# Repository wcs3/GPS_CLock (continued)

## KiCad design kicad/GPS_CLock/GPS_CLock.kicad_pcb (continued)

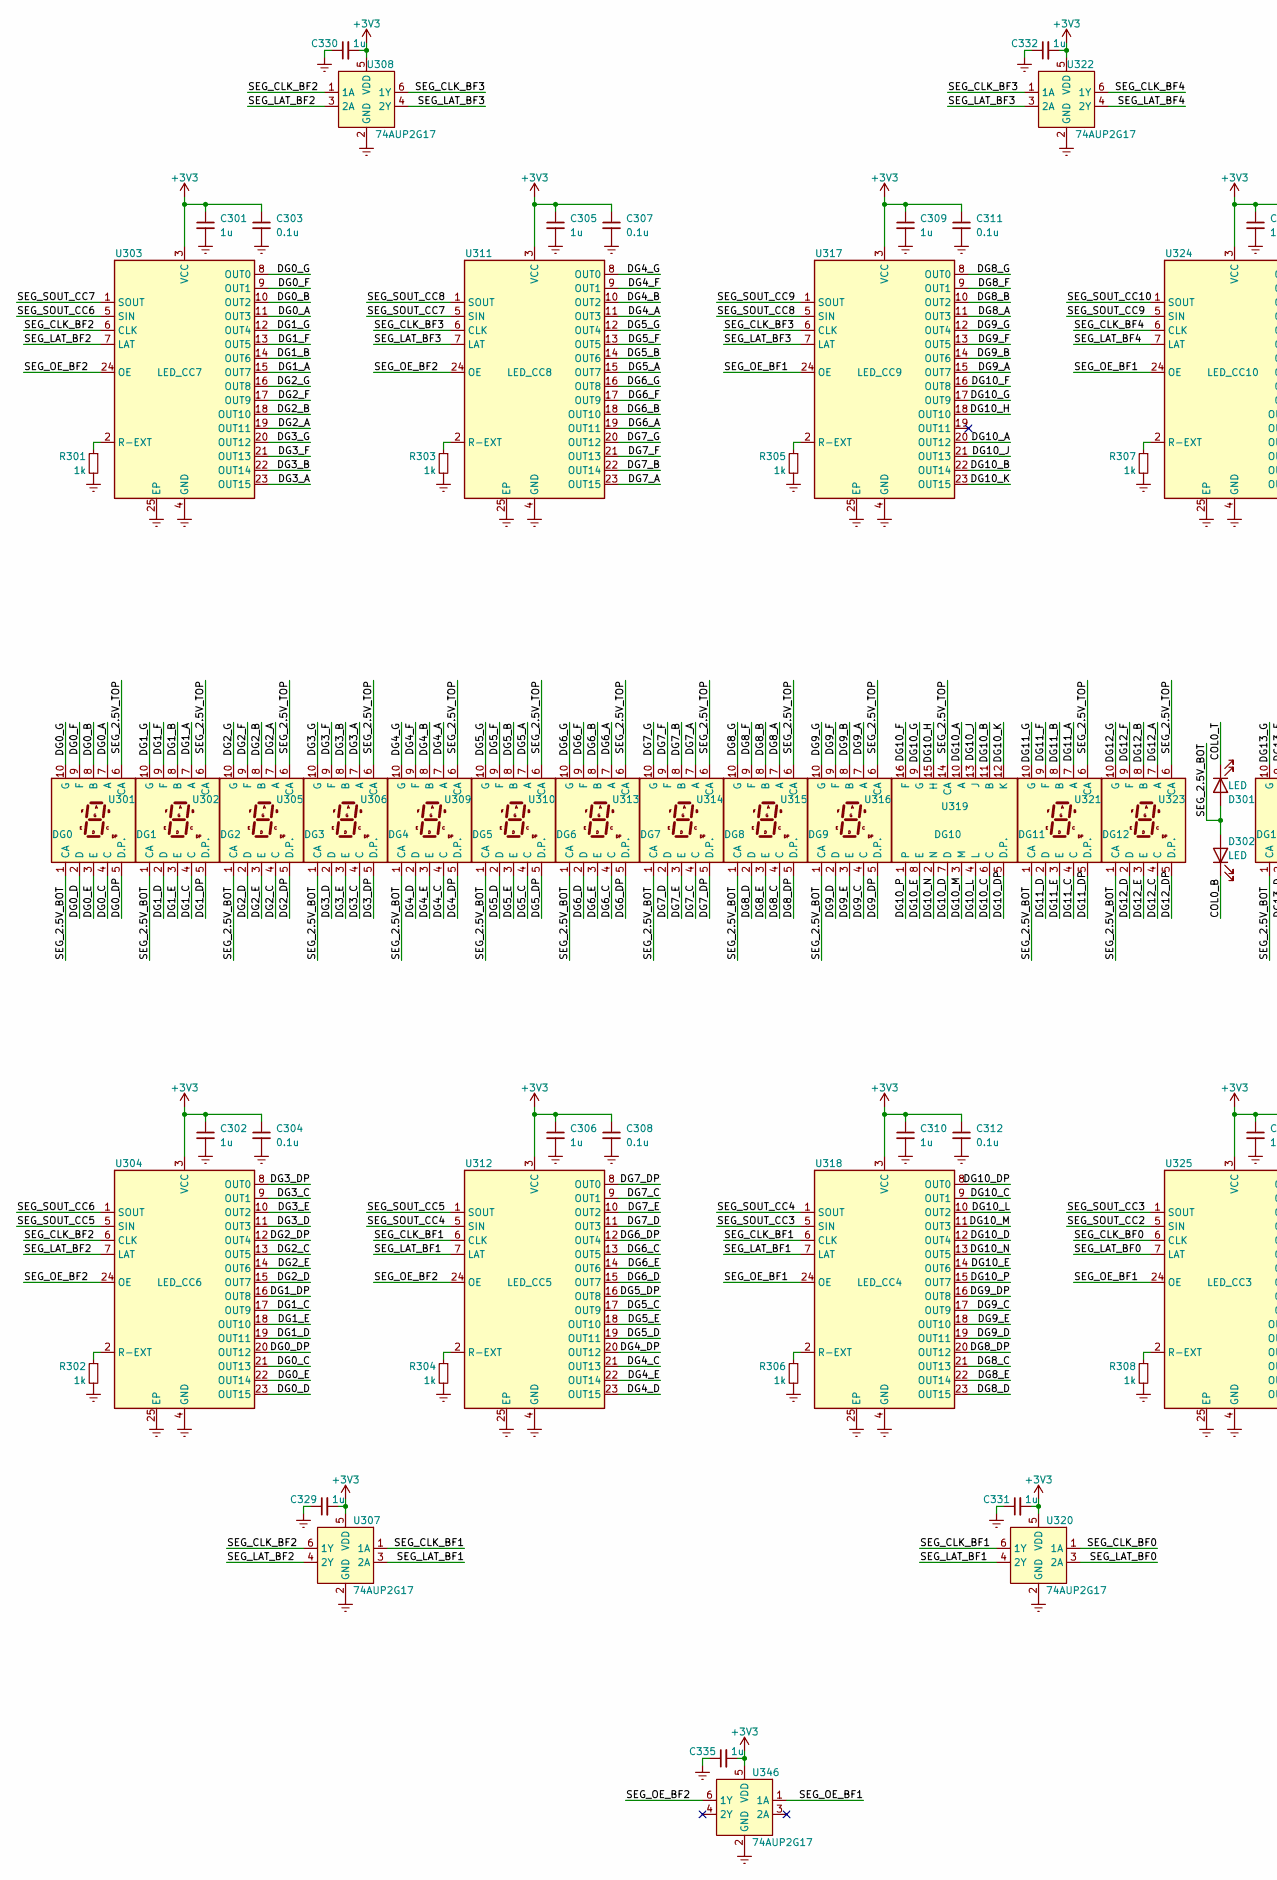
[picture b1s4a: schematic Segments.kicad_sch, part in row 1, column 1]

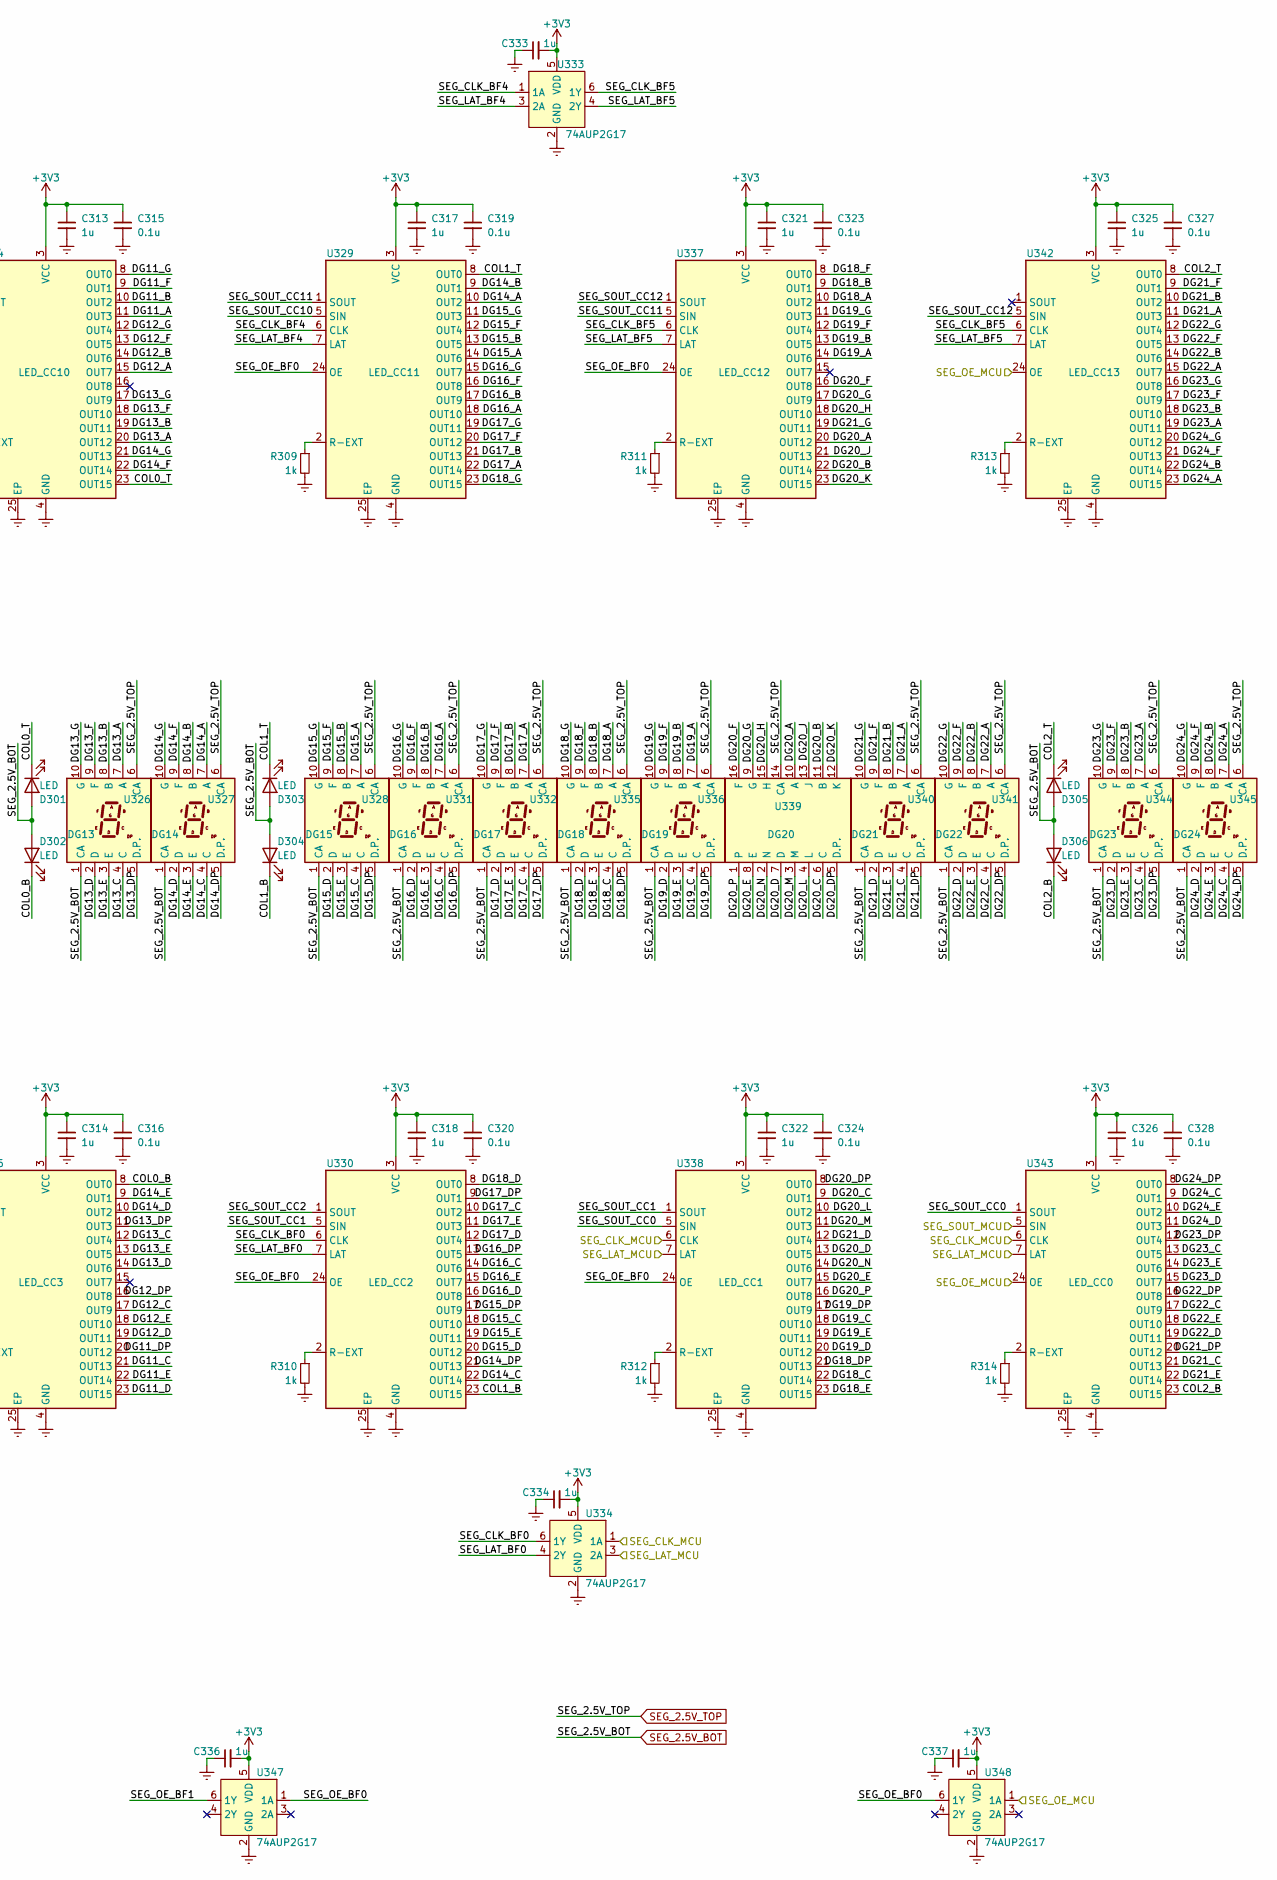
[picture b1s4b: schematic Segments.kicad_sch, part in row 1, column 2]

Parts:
C301, C302, C305, C306, C309, C310, C313, C314, C317, C318, C321, C322, C325, C326, C329, C330, C331, C332, C333, C334, C335, C336, C337: 1u; C_0402_1005Metric
C303, C304, C307, C308, C311, C312, C315, C316, C319, C320, C323, C324, C327, C328: 0.1u; C_0402_1005Metric
D301, D302, D303, D304, D305, D306: LED; LED_0805_2012Metric
R301, R302, R303, R304, R305, R306, R307, R308, R309, R310, R311, R312, R313, R314: 1k; R_0402_1005Metric
U301: DG0; 7seg 0.8in smd
U302: DG1; 7seg 0.8in smd
U303: LED_CC7; QFN-24-1EP_4x4mm_P0.5mm_EP2.6x2.6mm
U304: LED_CC6; QFN-24-1EP_4x4mm_P0.5mm_EP2.6x2.6mm
U305: DG2; 7seg 0.8in smd
U306: DG3; 7seg 0.8in smd
U307, U308, U320, U322, U333, U334, U346, U347, U348: 74AUP2G17; XSON-6_SOT886
U309: DG4; 7seg 0.8in smd
U310: DG5; 7seg 0.8in smd
U311: LED_CC8; QFN-24-1EP_4x4mm_P0.5mm_EP2.6x2.6mm
U312: LED_CC5; QFN-24-1EP_4x4mm_P0.5mm_EP2.6x2.6mm
U313: DG6; 7seg 0.8in smd
U314: DG7; 7seg 0.8in smd
U315: DG8; 7seg 0.8in smd
U316: DG9; 7seg 0.8in smd
U317: LED_CC9; QFN-24-1EP_4x4mm_P0.5mm_EP2.6x2.6mm
U318: LED_CC4; QFN-24-1EP_4x4mm_P0.5mm_EP2.6x2.6mm
U319: DG10; 14seg 0.4in smd
U321: DG11; 7seg 0.8in smd
U323: DG12; 7seg 0.8in smd
U324: LED_CC10; QFN-24-1EP_4x4mm_P0.5mm_EP2.6x2.6mm
U325: LED_CC3; QFN-24-1EP_4x4mm_P0.5mm_EP2.6x2.6mm
U326: DG13; 7seg 0.8in smd
U327: DG14; 7seg 0.8in smd
U328: DG15; 7seg 0.8in smd
U329: LED_CC11; QFN-24-1EP_4x4mm_P0.5mm_EP2.6x2.6mm
U330: LED_CC2; QFN-24-1EP_4x4mm_P0.5mm_EP2.6x2.6mm
U331: DG16; 7seg 0.8in smd
U332: DG17; 7seg 0.8in smd
U335: DG18; 7seg 0.8in smd
U336: DG19; 7seg 0.8in smd
U337: LED_CC12; QFN-24-1EP_4x4mm_P0.5mm_EP2.6x2.6mm
U338: LED_CC1; QFN-24-1EP_4x4mm_P0.5mm_EP2.6x2.6mm
U339: DG20; 14seg 0.4in smd
U340: DG21; 7seg 0.8in smd
U341: DG22; 7seg 0.8in smd
U342: LED_CC13; QFN-24-1EP_4x4mm_P0.5mm_EP2.6x2.6mm
U343: LED_CC0; QFN-24-1EP_4x4mm_P0.5mm_EP2.6x2.6mm
U344: DG23; 7seg 0.8in smd
U345: DG24; 7seg 0.8in smd

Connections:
+3V3: C301.1, C302.1, C303.1, C304.1, C305.1, C306.1, C307.1, C308.1, C309.1, C310.1, C311.1, C312.1, C313.1, C314.1, C315.1, C316.1, C317.1, C318.1, C319.1, C320.1, C321.1, C322.1, C323.1, C324.1, C325.1, C326.1, C327.1, C328.1, C329.2, C330.2, C331.2, C332.2, C333.2, C334.2, C335.2, C336.2, C337.2, U303.3 (VCC), U304.3 (VCC), U307.5 (VDD), U308.5 (VDD), U311.3 (VCC), U312.3 (VCC), U317.3 (VCC), U318.3 (VCC), U320.5 (VDD), U322.5 (VDD), U324.3 (VCC), U325.3 (VCC), U329.3 (VCC), U330.3 (VCC), U333.5 (VDD), U334.5 (VDD), U337.3 (VCC), U338.3 (VCC), U342.3 (VCC), U343.3 (VCC), U346.5 (VDD), U347.5 (VDD), U348.5 (VDD); also elsewhere on the board
/SEG_CLK: U334.1 (1A), U338.6 (CLK), U343.6 (CLK); also elsewhere on the board
/SEG_LAT: U334.3 (2A), U338.7 (LAT), U343.7 (LAT); also elsewhere on the board
/SEG_MOSI: U343.5 (SIN); also elsewhere on the board
/SEG_OE: U342.24 (OE), U343.24 (OE), U348.1 (1A); also elsewhere on the board
/Segments/COL0_B: D302.1 (K), U325.8 (OUT0)
/Segments/COL0_T: D301.1 (K), U324.23 (OUT15)
/Segments/COL1_B: D304.1 (K), U330.23 (OUT15)
/Segments/COL1_T: D303.1 (K), U329.8 (OUT0)
/Segments/COL2_B: D306.1 (K), U343.23 (OUT15)
/Segments/COL2_T: D305.1 (K), U342.8 (OUT0)
/Segments/DG0_A: U301.7 (A), U303.11 (OUT3)
/Segments/DG0_B: U301.8 (B), U303.10 (OUT2)
/Segments/DG0_C: U301.4 (C), U304.21 (OUT13)
/Segments/DG0_D: U301.2 (D), U304.23 (OUT15)
/Segments/DG0_DP: U301.5 (D.P.), U304.20 (OUT12)
/Segments/DG0_E: U301.3 (E), U304.22 (OUT14)
/Segments/DG0_F: U301.9 (F), U303.9 (OUT1)
/Segments/DG0_G: U301.10 (G), U303.8 (OUT0)
/Segments/DG1_A: U302.7 (A), U303.15 (OUT7)
/Segments/DG1_B: U302.8 (B), U303.14 (OUT6)
/Segments/DG1_C: U302.4 (C), U304.17 (OUT9)
/Segments/DG1_D: U302.2 (D), U304.19 (OUT11)
/Segments/DG1_DP: U302.5 (D.P.), U304.16 (OUT8)
/Segments/DG1_E: U302.3 (E), U304.18 (OUT10)
/Segments/DG1_F: U302.9 (F), U303.13 (OUT5)
/Segments/DG1_G: U302.10 (G), U303.12 (OUT4)
/Segments/DG2_A: U303.19 (OUT11), U305.7 (A)
/Segments/DG2_B: U303.18 (OUT10), U305.8 (B)
/Segments/DG2_C: U304.13 (OUT5), U305.4 (C)
/Segments/DG2_D: U304.15 (OUT7), U305.2 (D)
/Segments/DG2_DP: U304.12 (OUT4), U305.5 (D.P.)
/Segments/DG2_E: U304.14 (OUT6), U305.3 (E)
/Segments/DG2_F: U303.17 (OUT9), U305.9 (F)
/Segments/DG2_G: U303.16 (OUT8), U305.10 (G)
/Segments/DG3_A: U303.23 (OUT15), U306.7 (A)
/Segments/DG3_B: U303.22 (OUT14), U306.8 (B)
/Segments/DG3_C: U304.9 (OUT1), U306.4 (C)
/Segments/DG3_D: U304.11 (OUT3), U306.2 (D)
/Segments/DG3_DP: U304.8 (OUT0), U306.5 (D.P.)
/Segments/DG3_E: U304.10 (OUT2), U306.3 (E)
/Segments/DG3_F: U303.21 (OUT13), U306.9 (F)
/Segments/DG3_G: U303.20 (OUT12), U306.10 (G)
/Segments/DG4_A: U309.7 (A), U311.11 (OUT3)
/Segments/DG4_B: U309.8 (B), U311.10 (OUT2)
/Segments/DG4_C: U309.4 (C), U312.21 (OUT13)
/Segments/DG4_D: U309.2 (D), U312.23 (OUT15)
/Segments/DG4_DP: U309.5 (D.P.), U312.20 (OUT12)
/Segments/DG4_E: U309.3 (E), U312.22 (OUT14)
/Segments/DG4_F: U309.9 (F), U311.9 (OUT1)
/Segments/DG4_G: U309.10 (G), U311.8 (OUT0)
/Segments/DG5_A: U310.7 (A), U311.15 (OUT7)
/Segments/DG5_B: U310.8 (B), U311.14 (OUT6)
/Segments/DG5_C: U310.4 (C), U312.17 (OUT9)
/Segments/DG5_D: U310.2 (D), U312.19 (OUT11)
/Segments/DG5_DP: U310.5 (D.P.), U312.16 (OUT8)
/Segments/DG5_E: U310.3 (E), U312.18 (OUT10)
/Segments/DG5_F: U310.9 (F), U311.13 (OUT5)
/Segments/DG5_G: U310.10 (G), U311.12 (OUT4)
/Segments/DG6_A: U311.19 (OUT11), U313.7 (A)
/Segments/DG6_B: U311.18 (OUT10), U313.8 (B)
/Segments/DG6_C: U312.13 (OUT5), U313.4 (C)
/Segments/DG6_D: U312.15 (OUT7), U313.2 (D)
/Segments/DG6_DP: U312.12 (OUT4), U313.5 (D.P.)
/Segments/DG6_E: U312.14 (OUT6), U313.3 (E)
/Segments/DG6_F: U311.17 (OUT9), U313.9 (F)
/Segments/DG6_G: U311.16 (OUT8), U313.10 (G)
/Segments/DG7_A: U311.23 (OUT15), U314.7 (A)
/Segments/DG7_B: U311.22 (OUT14), U314.8 (B)
/Segments/DG7_C: U312.9 (OUT1), U314.4 (C)
/Segments/DG7_D: U312.11 (OUT3), U314.2 (D)
/Segments/DG7_DP: U312.8 (OUT0), U314.5 (D.P.)
/Segments/DG7_E: U312.10 (OUT2), U314.3 (E)
/Segments/DG7_F: U311.21 (OUT13), U314.9 (F)
/Segments/DG7_G: U311.20 (OUT12), U314.10 (G)
/Segments/DG8_A: U315.7 (A), U317.11 (OUT3)
/Segments/DG8_B: U315.8 (B), U317.10 (OUT2)
/Segments/DG8_C: U315.4 (C), U318.21 (OUT13)
/Segments/DG8_D: U315.2 (D), U318.23 (OUT15)
/Segments/DG8_DP: U315.5 (D.P.), U318.20 (OUT12)
/Segments/DG8_E: U315.3 (E), U318.22 (OUT14)
/Segments/DG8_F: U315.9 (F), U317.9 (OUT1)
/Segments/DG8_G: U315.10 (G), U317.8 (OUT0)
/Segments/DG9_A: U316.7 (A), U317.15 (OUT7)
/Segments/DG9_B: U316.8 (B), U317.14 (OUT6)
/Segments/DG9_C: U316.4 (C), U318.17 (OUT9)
/Segments/DG9_D: U316.2 (D), U318.19 (OUT11)
/Segments/DG9_DP: U316.5 (D.P.), U318.16 (OUT8)
/Segments/DG9_E: U316.3 (E), U318.18 (OUT10)
/Segments/DG9_F: U316.9 (F), U317.13 (OUT5)
/Segments/DG9_G: U316.10 (G), U317.12 (OUT4)
/Segments/DG10_A: U317.20 (OUT12), U319.10 (A)
/Segments/DG10_B: U317.22 (OUT14), U319.11 (B)
/Segments/DG10_C: U318.9 (OUT1), U319.6 (C)
/Segments/DG10_D: U318.12 (OUT4), U319.7 (D)
/Segments/DG10_DP: U318.8 (OUT0), U319.5 (D.P.)
/Segments/DG10_E: U318.14 (OUT6), U319.8 (E)
/Segments/DG10_F: U317.16 (OUT8), U319.16 (F)
/Segments/DG10_G: U317.17 (OUT9), U319.9 (G)
/Segments/DG10_H: U317.18 (OUT10), U319.15 (H)
/Segments/DG10_J: U317.21 (OUT13), U319.13 (J)
/Segments/DG10_K: U317.23 (OUT15), U319.12 (K)
/Segments/DG10_L: U318.10 (OUT2), U319.4 (L)
/Segments/DG10_M: U318.11 (OUT3), U319.3 (M)
/Segments/DG10_N: U318.13 (OUT5), U319.2 (N)
/Segments/DG10_P: U318.15 (OUT7), U319.1
/Segments/DG11_A: U321.7 (A), U324.11 (OUT3)
/Segments/DG11_B: U321.8 (B), U324.10 (OUT2)
/Segments/DG11_C: U321.4 (C), U325.21 (OUT13)
/Segments/DG11_D: U321.2 (D), U325.23 (OUT15)
/Segments/DG11_DP: U321.5 (D.P.), U325.20 (OUT12)
/Segments/DG11_E: U321.3 (E), U325.22 (OUT14)
/Segments/DG11_F: U321.9 (F), U324.9 (OUT1)
/Segments/DG11_G: U321.10 (G), U324.8 (OUT0)
/Segments/DG12_A: U323.7 (A), U324.15 (OUT7)
/Segments/DG12_B: U323.8 (B), U324.14 (OUT6)
/Segments/DG12_C: U323.4 (C), U325.17 (OUT9)
/Segments/DG12_D: U323.2 (D), U325.19 (OUT11)
/Segments/DG12_DP: U323.5 (D.P.), U325.16 (OUT8)
/Segments/DG12_E: U323.3 (E), U325.18 (OUT10)
/Segments/DG12_F: U323.9 (F), U324.13 (OUT5)
/Segments/DG12_G: U323.10 (G), U324.12 (OUT4)
/Segments/DG13_A: U324.20 (OUT12), U326.7 (A)
/Segments/DG13_B: U324.19 (OUT11), U326.8 (B)
/Segments/DG13_C: U325.12 (OUT4), U326.4 (C)
/Segments/DG13_D: U325.14 (OUT6), U326.2 (D)
/Segments/DG13_DP: U325.11 (OUT3), U326.5 (D.P.)
/Segments/DG13_E: U325.13 (OUT5), U326.3 (E)
/Segments/DG13_F: U324.18 (OUT10), U326.9 (F)
/Segments/DG13_G: U324.17 (OUT9), U326.10 (G)
/Segments/DG14_A: U327.7 (A), U329.10 (OUT2)
/Segments/DG14_B: U327.8 (B), U329.9 (OUT1)
/Segments/DG14_C: U327.4 (C), U330.22 (OUT14)
/Segments/DG14_D: U325.10 (OUT2), U327.2 (D)
/Segments/DG14_DP: U327.5 (D.P.), U330.21 (OUT13)
/Segments/DG14_E: U325.9 (OUT1), U327.3 (E)
/Segments/DG14_F: U324.22 (OUT14), U327.9 (F)
/Segments/DG14_G: U324.21 (OUT13), U327.10 (G)
/Segments/DG15_A: U328.7 (A), U329.14 (OUT6)
/Segments/DG15_B: U328.8 (B), U329.13 (OUT5)
/Segments/DG15_C: U328.4 (C), U330.18 (OUT10)
/Segments/DG15_D: U328.2 (D), U330.20 (OUT12)
/Segments/DG15_DP: U328.5 (D.P.), U330.17 (OUT9)
/Segments/DG15_E: U328.3 (E), U330.19 (OUT11)
/Segments/DG15_F: U328.9 (F), U329.12 (OUT4)
/Segments/DG15_G: U328.10 (G), U329.11 (OUT3)
/Segments/DG16_A: U329.18 (OUT10), U331.7 (A)
/Segments/DG16_B: U329.17 (OUT9), U331.8 (B)
/Segments/DG16_C: U330.14 (OUT6), U331.4 (C)
/Segments/DG16_D: U330.16 (OUT8), U331.2 (D)
/Segments/DG16_DP: U330.13 (OUT5), U331.5 (D.P.)
/Segments/DG16_E: U330.15 (OUT7), U331.3 (E)
/Segments/DG16_F: U329.16 (OUT8), U331.9 (F)
/Segments/DG16_G: U329.15 (OUT7), U331.10 (G)
/Segments/DG17_A: U329.22 (OUT14), U332.7 (A)
/Segments/DG17_B: U329.21 (OUT13), U332.8 (B)
/Segments/DG17_C: U330.10 (OUT2), U332.4 (C)
/Segments/DG17_D: U330.12 (OUT4), U332.2 (D)
/Segments/DG17_DP: U330.9 (OUT1), U332.5 (D.P.)
/Segments/DG17_E: U330.11 (OUT3), U332.3 (E)
/Segments/DG17_F: U329.20 (OUT12), U332.9 (F)
/Segments/DG17_G: U329.19 (OUT11), U332.10 (G)
/Segments/DG18_A: U335.7 (A), U337.10 (OUT2)
/Segments/DG18_B: U335.8 (B), U337.9 (OUT1)
/Segments/DG18_C: U335.4 (C), U338.22 (OUT14)
/Segments/DG18_D: U330.8 (OUT0), U335.2 (D)
/Segments/DG18_DP: U335.5 (D.P.), U338.21 (OUT13)
/Segments/DG18_E: U335.3 (E), U338.23 (OUT15)
/Segments/DG18_F: U335.9 (F), U337.8 (OUT0)
/Segments/DG18_G: U329.23 (OUT15), U335.10 (G)
/Segments/DG19_A: U336.7 (A), U337.14 (OUT6)
/Segments/DG19_B: U336.8 (B), U337.13 (OUT5)
/Segments/DG19_C: U336.4 (C), U338.18 (OUT10)
/Segments/DG19_D: U336.2 (D), U338.20 (OUT12)
/Segments/DG19_DP: U336.5 (D.P.), U338.17 (OUT9)
/Segments/DG19_E: U336.3 (E), U338.19 (OUT11)
/Segments/DG19_F: U336.9 (F), U337.12 (OUT4)
/Segments/DG19_G: U336.10 (G), U337.11 (OUT3)
/Segments/DG20_A: U337.20 (OUT12), U339.10 (A)
/Segments/DG20_B: U337.22 (OUT14), U339.11 (B)
/Segments/DG20_C: U338.9 (OUT1), U339.6 (C)
/Segments/DG20_D: U338.13 (OUT5), U339.7 (D)
/Segments/DG20_DP: U338.8 (OUT0), U339.5 (D.P.)
/Segments/DG20_E: U338.15 (OUT7), U339.8 (E)
/Segments/DG20_F: U337.16 (OUT8), U339.16 (F)
/Segments/DG20_G: U337.17 (OUT9), U339.9 (G)
/Segments/DG20_H: U337.18 (OUT10), U339.15 (H)
/Segments/DG20_J: U337.21 (OUT13), U339.13 (J)
/Segments/DG20_K: U337.23 (OUT15), U339.12 (K)
/Segments/DG20_L: U338.10 (OUT2), U339.4 (L)
/Segments/DG20_M: U338.11 (OUT3), U339.3 (M)
/Segments/DG20_N: U338.14 (OUT6), U339.2 (N)
/Segments/DG20_P: U338.16 (OUT8), U339.1
/Segments/DG21_A: U340.7 (A), U342.11 (OUT3)
/Segments/DG21_B: U340.8 (B), U342.10 (OUT2)
/Segments/DG21_C: U340.4 (C), U343.21 (OUT13)
/Segments/DG21_D: U338.12 (OUT4), U340.2 (D)
/Segments/DG21_DP: U340.5 (D.P.), U343.20 (OUT12)
/Segments/DG21_E: U340.3 (E), U343.22 (OUT14)
/Segments/DG21_F: U340.9 (F), U342.9 (OUT1)
/Segments/DG21_G: U337.19 (OUT11), U340.10 (G)
/Segments/DG22_A: U341.7 (A), U342.15 (OUT7)
/Segments/DG22_B: U341.8 (B), U342.14 (OUT6)
/Segments/DG22_C: U341.4 (C), U343.17 (OUT9)
/Segments/DG22_D: U341.2 (D), U343.19 (OUT11)
/Segments/DG22_DP: U341.5 (D.P.), U343.16 (OUT8)
/Segments/DG22_E: U341.3 (E), U343.18 (OUT10)
/Segments/DG22_F: U341.9 (F), U342.13 (OUT5)
/Segments/DG22_G: U341.10 (G), U342.12 (OUT4)
/Segments/DG23_A: U342.19 (OUT11), U344.7 (A)
/Segments/DG23_B: U342.18 (OUT10), U344.8 (B)
/Segments/DG23_C: U343.13 (OUT5), U344.4 (C)
/Segments/DG23_D: U343.15 (OUT7), U344.2 (D)
/Segments/DG23_DP: U343.12 (OUT4), U344.5 (D.P.)
/Segments/DG23_E: U343.14 (OUT6), U344.3 (E)
/Segments/DG23_F: U342.17 (OUT9), U344.9 (F)
/Segments/DG23_G: U342.16 (OUT8), U344.10 (G)
/Segments/DG24_A: U342.23 (OUT15), U345.7 (A)
/Segments/DG24_B: U342.22 (OUT14), U345.8 (B)
/Segments/DG24_C: U343.9 (OUT1), U345.4 (C)
/Segments/DG24_D: U343.11 (OUT3), U345.2 (D)
/Segments/DG24_DP: U343.8 (OUT0), U345.5 (D.P.)
/Segments/DG24_E: U343.10 (OUT2), U345.3 (E)
/Segments/DG24_F: U342.21 (OUT13), U345.9 (F)
/Segments/DG24_G: U342.20 (OUT12), U345.10 (G)
/Segments/SEG_CLK_BF0: U320.1 (1A), U325.6 (CLK), U330.6 (CLK), U334.6 (1Y)
/Segments/SEG_CLK_BF1: U307.1 (1A), U312.6 (CLK), U318.6 (CLK), U320.6 (1Y)
/Segments/SEG_CLK_BF2: U303.6 (CLK), U304.6 (CLK), U307.6 (1Y), U308.1 (1A)
/Segments/SEG_CLK_BF3: U308.6 (1Y), U311.6 (CLK), U317.6 (CLK), U322.1 (1A)
/Segments/SEG_CLK_BF4: U322.6 (1Y), U324.6 (CLK), U329.6 (CLK), U333.1 (1A)
/Segments/SEG_CLK_BF5: U333.6 (1Y), U337.6 (CLK), U342.6 (CLK)
/Segments/SEG_LAT_BF0: U320.3 (2A), U325.7 (LAT), U330.7 (LAT), U334.4 (2Y)
/Segments/SEG_LAT_BF1: U307.3 (2A), U312.7 (LAT), U318.7 (LAT), U320.4 (2Y)
/Segments/SEG_LAT_BF2: U303.7 (LAT), U304.7 (LAT), U307.4 (2Y), U308.3 (2A)
/Segments/SEG_LAT_BF3: U308.4 (2Y), U311.7 (LAT), U317.7 (LAT), U322.3 (2A)
/Segments/SEG_LAT_BF4: U322.4 (2Y), U324.7 (LAT), U329.7 (LAT), U333.3 (2A)
/Segments/SEG_LAT_BF5: U333.4 (2Y), U337.7 (LAT), U342.7 (LAT)
/Segments/SEG_OE_BF0: U329.24 (OE), U330.24 (OE), U337.24 (OE), U338.24 (OE), U347.1 (1A), U348.6 (1Y)
/Segments/SEG_OE_BF1: U317.24 (OE), U318.24 (OE), U324.24 (OE), U325.24 (OE), U346.1 (1A), U347.6 (1Y)
/Segments/SEG_OE_BF2: U303.24 (OE), U304.24 (OE), U311.24 (OE), U312.24 (OE), U346.6 (1Y)
/Segments/SEG_SOUT_CC0: U338.5 (SIN), U343.1 (SOUT)
/Segments/SEG_SOUT_CC1: U330.5 (SIN), U338.1 (SOUT)
/Segments/SEG_SOUT_CC2: U325.5 (SIN), U330.1 (SOUT)
/Segments/SEG_SOUT_CC3: U318.5 (SIN), U325.1 (SOUT)
/Segments/SEG_SOUT_CC4: U312.5 (SIN), U318.1 (SOUT)
/Segments/SEG_SOUT_CC5: U304.5 (SIN), U312.1 (SOUT)
/Segments/SEG_SOUT_CC6: U303.5 (SIN), U304.1 (SOUT)
/Segments/SEG_SOUT_CC7: U303.1 (SOUT), U311.5 (SIN)
/Segments/SEG_SOUT_CC8: U311.1 (SOUT), U317.5 (SIN)
/Segments/SEG_SOUT_CC9: U317.1 (SOUT), U324.5 (SIN)
/Segments/SEG_SOUT_CC10: U324.1 (SOUT), U329.5 (SIN)
/Segments/SEG_SOUT_CC11: U329.1 (SOUT), U337.5 (SIN)
/Segments/SEG_SOUT_CC12: U337.1 (SOUT), U342.5 (SIN)
Earth: C301.2, C302.2, C303.2, C304.2, C305.2, C306.2, C307.2, C308.2, C309.2, C310.2, C311.2, C312.2, C313.2, C314.2, C315.2, C316.2, C317.2, C318.2, C319.2, C320.2, C321.2, C322.2, C323.2, C324.2, C325.2, C326.2, C327.2, C328.2, C329.1, C330.1, C331.1, C332.1, C333.1, C334.1, C335.1, C336.1, C337.1, R301.2, R302.2, R303.2, R304.2, R305.2, R306.2, R307.2, R308.2, R309.2, R310.2, R311.2, R312.2, R313.2, R314.2, U303.4 (GND), U303.25 (EP), U304.4 (GND), U304.25 (EP), U307.2 (GND), U308.2 (GND), U311.4 (GND), U311.25 (EP), U312.4 (GND), U312.25 (EP), U317.4 (GND), U317.25 (EP), U318.4 (GND), U318.25 (EP), U320.2 (GND), U322.2 (GND), U324.4 (GND), U324.25 (EP), U325.4 (GND), U325.25 (EP), U329.4 (GND), U329.25 (EP), U330.4 (GND), U330.25 (EP), U333.2 (GND), U334.2 (GND), U337.4 (GND), U337.25 (EP), U338.4 (GND), U338.25 (EP), U342.4 (GND), U342.25 (EP), U343.4 (GND), U343.25 (EP), U346.2 (GND), U347.2 (GND), U348.2 (GND); also elsewhere on the board
unnamed: R301.1, U303.2 (R-EXT)
unnamed: R302.1, U304.2 (R-EXT)
unnamed: R303.1, U311.2 (R-EXT)
unnamed: R304.1, U312.2 (R-EXT)
unnamed: R305.1, U317.2 (R-EXT)
unnamed: R306.1, U318.2 (R-EXT)
unnamed: R307.1, U324.2 (R-EXT)
unnamed: R308.1, U325.2 (R-EXT)
unnamed: R309.1, U329.2 (R-EXT)
unnamed: R310.1, U330.2 (R-EXT)
unnamed: R311.1, U337.2 (R-EXT)
unnamed: R312.1, U338.2 (R-EXT)
unnamed: R313.1, U342.2 (R-EXT)
unnamed: R314.1, U343.2 (R-EXT)
SEG_2.5V_BOT: D301.2 (A), D302.2 (A), D303.2 (A), D304.2 (A), D305.2 (A), D306.2 (A), U301.1 (CA), U302.1 (CA), U305.1 (CA), U306.1 (CA), U309.1 (CA), U310.1 (CA), U313.1 (CA), U314.1 (CA), U315.1 (CA), U316.1 (CA), U321.1 (CA), U323.1 (CA), U326.1 (CA), U327.1 (CA), U328.1 (CA), U331.1 (CA), U332.1 (CA), U335.1 (CA), U336.1 (CA), U340.1 (CA), U341.1 (CA), U344.1 (CA), U345.1 (CA); also elsewhere on the board
SEG_2.5V_TOP: U301.6 (CA), U302.6 (CA), U305.6 (CA), U306.6 (CA), U309.6 (CA), U310.6 (CA), U313.6 (CA), U314.6 (CA), U315.6 (CA), U316.6 (CA), U319.14 (CA), U321.6 (CA), U323.6 (CA), U326.6 (CA), U327.6 (CA), U328.6 (CA), U331.6 (CA), U332.6 (CA), U335.6 (CA), U336.6 (CA), U339.14 (CA), U340.6 (CA), U341.6 (CA), U344.6 (CA), U345.6 (CA); also elsewhere on the board

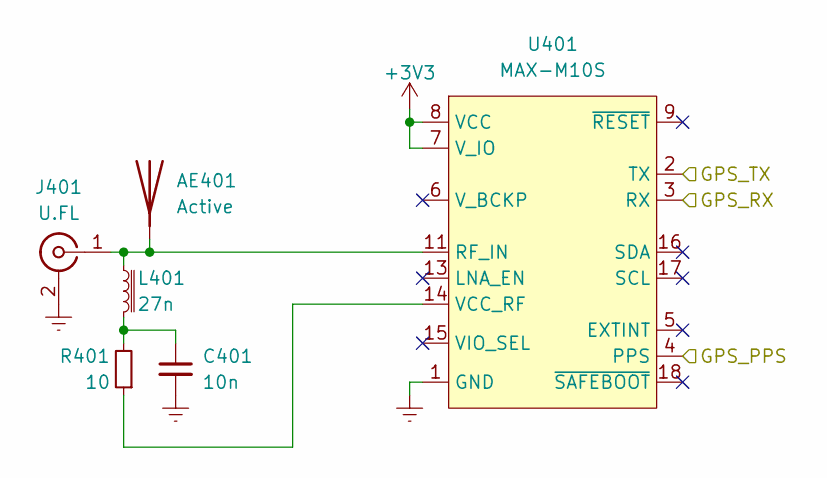
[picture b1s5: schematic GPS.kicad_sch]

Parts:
AE401: Active
C401: 10n; C_0402_1005Metric
J401: U.FL; U.FL_Hirose_U.FL-R-SMT-1_Vertical
L401: 27n; L_0402_1005Metric
R401: 10; R_0402_1005Metric
U401: MAX-M10S; UBLOX_MAX-M10S

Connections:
+3V3: U401.7 (V_IO), U401.8 (VCC); also elsewhere on the board
/GPS_PPS: U401.4 (PPS); also elsewhere on the board
/GPS_RX: U401.3 (RX); also elsewhere on the board
/GPS_TX: U401.2 (TX); also elsewhere on the board
Earth: C401.2, J401.2 (Ext), U401.1 (GND), U401.10 (GND), U401.12 (GND); also elsewhere on the board
unnamed: AE401.1, J401.1 (In), L401.1, U401.11 (RF_IN)
unnamed: C401.1, L401.2, R401.2
unnamed: R401.1, U401.14 (VCC_RF)

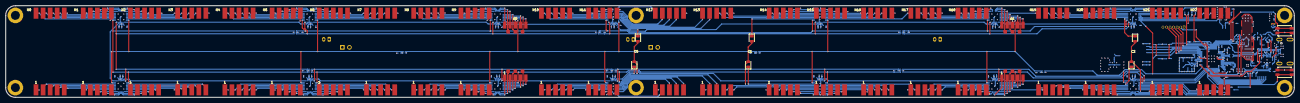
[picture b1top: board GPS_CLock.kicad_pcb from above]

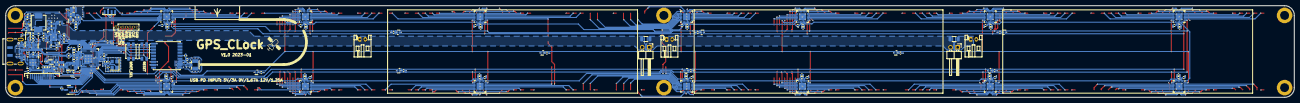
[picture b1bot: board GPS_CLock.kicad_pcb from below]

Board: 4 copper layers, 464.0 x 33.0 mm, 209 parts (170 on the bottom side), 343 nets.

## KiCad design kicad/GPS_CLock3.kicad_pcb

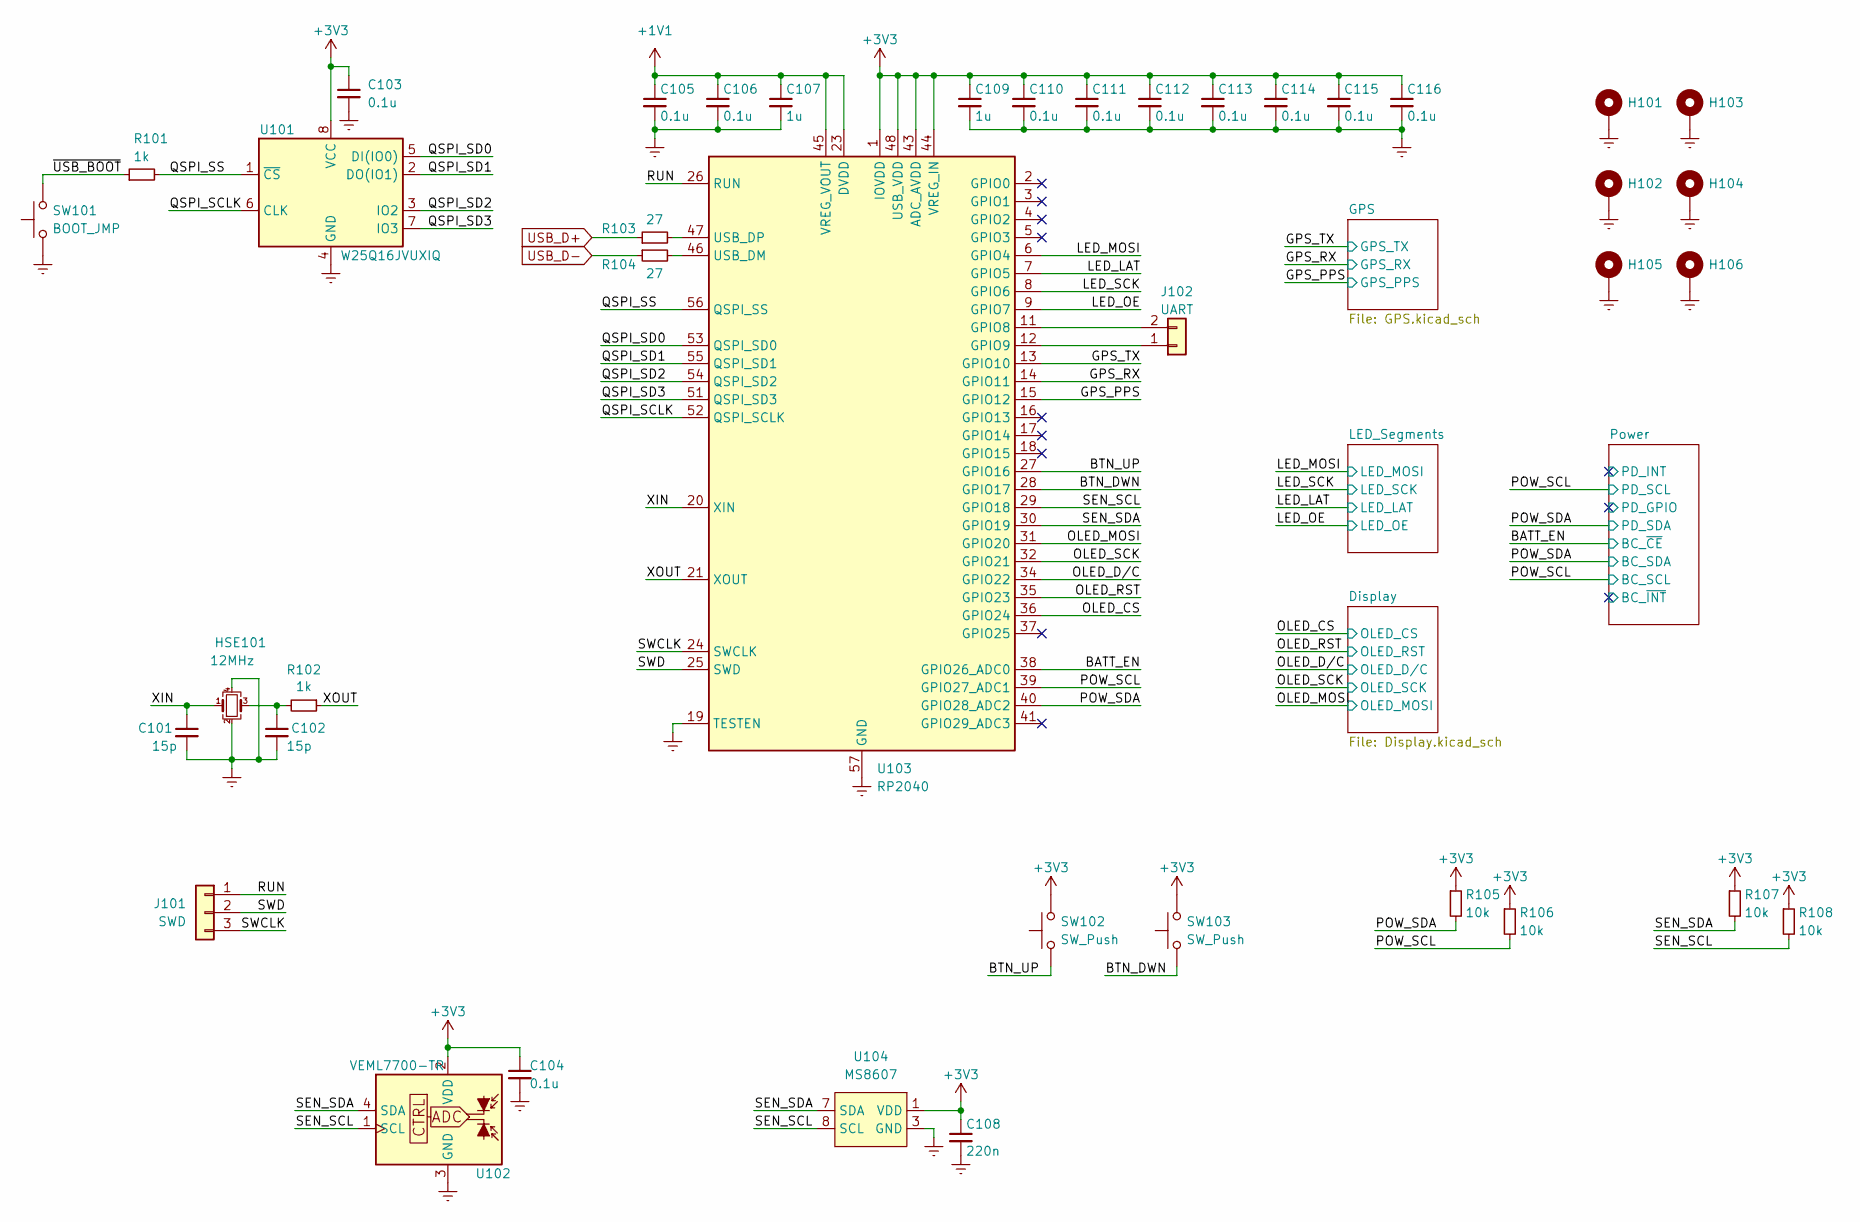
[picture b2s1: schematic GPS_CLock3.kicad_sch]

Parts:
C101, C102: 15p; C_0402_1005Metric
C103, C104, C105, C106, C110, C111, C112, C113, C114, C115, C116: 0.1u; C_0402_1005Metric
C107, C109: 1u; C_0402_1005Metric
C108: 220n; C_0402_1005Metric
H101, H102, H103, H104, H105, H106: MountingHole_Pad; MountingHole_2.2mm_M2_DIN965_Pad
HSE101: 12MHz; Crystal_SMD_3225-4Pin_3.2x2.5mm
J101: SWD; PinHeader_1x03_P1.27mm_Vertical
J102: UART; PinHeader_1x02_P1.27mm_Vertical
R101, R102: 1k; R_0402_1005Metric
R103, R104: 27; R_0402_1005Metric
R105, R106, R107, R108: 10k; R_0402_1005Metric
SW101: BOOT_JMP; EVQP4xB3x
SW102, SW103: SW_Push; EVQP4xB3x
U101: W25Q16JVUXIQ; WINBOND_USON-8_2x3mm
U102: VEML7700-TR; VEML7700
U103: RP2040; QFN-56-1EP_7x7mm_P0.4mm_EP3.2x3.2mm
U104: MS8607

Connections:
+1V1: C105.1, C106.1, C107.1, U103.23 (DVDD), U103.45 (VREG_VOUT), U103.50 (DVDD)
+3V3: C103.1, C104.1, C108.1, C109.1, C110.1, C111.1, C112.1, C113.1, C114.1, C115.1, C116.1, R105.1, R106.1, R107.1, R108.1, SW102.1, SW103.1, U101.8 (VCC), U102.2 (VDD), U103.1 (IOVDD), U103.10 (IOVDD), U103.22 (IOVDD), U103.33 (IOVDD), U103.42 (IOVDD), U103.43 (ADC_AVDD), U103.44 (VREG_IN), U103.48 (USB_VDD), U103.49 (IOVDD), U104.1 (VDD); also elsewhere on the board
/BATT_EN: U103.38 (GPIO26_ADC0); also elsewhere on the board
/BTN_DWN: SW103.2, U103.28 (GPIO17)
/BTN_UP: SW102.2, U103.27 (GPIO16)
/GPS_PPS: U103.15 (GPIO12); also elsewhere on the board
/GPS_RX: U103.14 (GPIO11); also elsewhere on the board
/GPS_TX: U103.13 (GPIO10); also elsewhere on the board
/LED_LAT: U103.7 (GPIO5); also elsewhere on the board
/LED_MOSI: U103.6 (GPIO4); also elsewhere on the board
/LED_OE: U103.9 (GPIO7); also elsewhere on the board
/LED_SCK: U103.8 (GPIO6); also elsewhere on the board
/OLED_CS: U103.36 (GPIO24); also elsewhere on the board
/OLED_D/C: U103.34 (GPIO22); also elsewhere on the board
/OLED_MOSI: U103.31 (GPIO20); also elsewhere on the board
/OLED_RST: U103.35 (GPIO23); also elsewhere on the board
/OLED_SCK: U103.32 (GPIO21); also elsewhere on the board
/POW_SCL: R106.2, U103.39 (GPIO27_ADC1); also elsewhere on the board
/POW_SDA: R105.2, U103.40 (GPIO28_ADC2); also elsewhere on the board
/QSPI_SCLK: U101.6 (CLK), U103.52 (QSPI_SCLK)
/QSPI_SD0: U101.5 (DI(IO0)), U103.53 (QSPI_SD0)
/QSPI_SD1: U101.2 (DO(IO1)), U103.55 (QSPI_SD1)
/QSPI_SD2: U101.3 (IO2), U103.54 (QSPI_SD2)
/QSPI_SD3: U101.7 (IO3), U103.51 (QSPI_SD3)
/QSPI_SS: R101.2, U101.1 (~CS), U103.56 (QSPI_SS)
/RUN: J101.1, U103.26 (RUN)
/SEN_SCL: R108.2, U102.1 (SCL), U103.29 (GPIO18), U104.8 (SCL)
/SEN_SDA: R107.2, U102.4 (SDA), U103.30 (GPIO19), U104.7 (SDA)
/SWCLK: J101.3, U103.24 (SWCLK)
/SWD: J101.2, U103.25 (SWD)
/XIN: C101.1, HSE101.1, U103.20 (XIN)
/XOUT: R102.1, U103.21 (XOUT)
/~USB_BOOT: R101.1, SW101.1
Earth: C101.2, C102.2, C103.2, C104.2, C105.2, C106.2, C107.2, C108.2, C109.2, C110.2, C111.2, C112.2, C113.2, C114.2, C115.2, C116.2, H101.1, H102.1, H103.1, H104.1, H105.1, H106.1, HSE101.2, HSE101.4, SW101.2, U101.4 (GND), U102.3 (GND), U103.19 (TESTEN), U103.57 (GND), U104.3 (GND); also elsewhere on the board
unnamed: C102.1, HSE101.3, R102.2
unnamed: J102.1, U103.12 (GPIO9)
unnamed: J102.2, U103.11 (GPIO8)
unnamed: R103.2, U103.47 (USB_DP)
unnamed: R104.2, U103.46 (USB_DM)
USB_D+: R103.1; also elsewhere on the board
USB_D-: R104.1; also elsewhere on the board
